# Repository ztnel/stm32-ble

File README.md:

# stm32-ble
STM32 Bluetooth Hardware Design Files

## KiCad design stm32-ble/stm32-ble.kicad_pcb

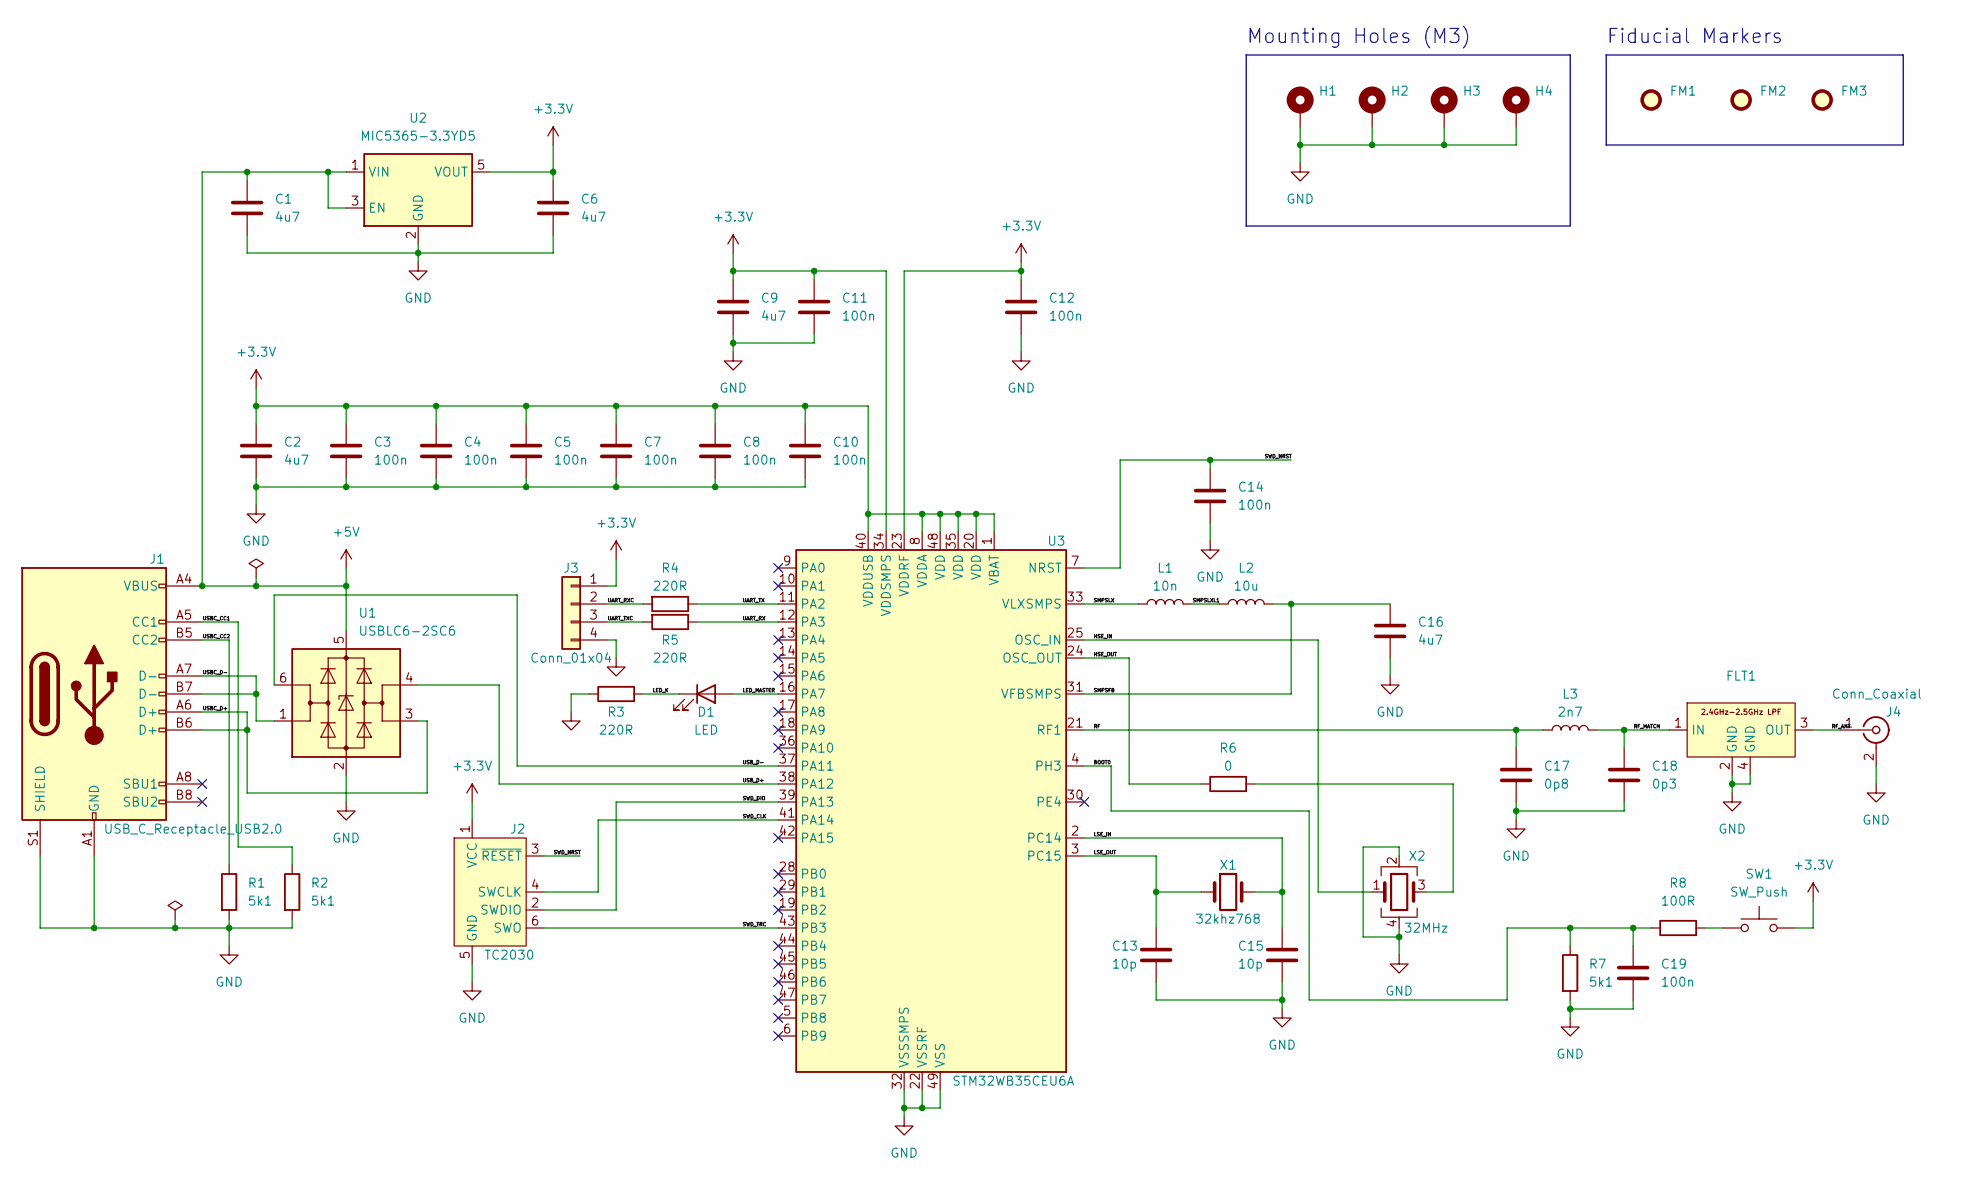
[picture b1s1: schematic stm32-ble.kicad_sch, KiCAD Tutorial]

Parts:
C1, C2, C6, C9, C16: 4u7; C_0603_1608Metric
C3, C4, C5, C7, C8, C10, C11, C12, C14, C19: 100n; C_0402_1005Metric
C13, C15: 10p; C_0402_1005Metric
C17: 0p8; C_0402_1005Metric
C18: 0p3; C_0402_1005Metric
D1: LED; LED_0402_1005Metric
FLT1: DLF162500LT-5028A1
FM1, FM2, FM3: Fiducial; Fiducial_1mm_Mask2mm
H1, H2, H3, H4: MountingHole_Pad; MountingHole_2.2mm_M2_Pad_Via
J1: USB_C_Receptacle_USB2.0; USB_C_Receptacle_GCT_USB4105-xx-A_16P_TopMnt_Horizontal
J2: TC2030; Tag-Connect_TC2030-IDC-FP_2x03_P1.27mm_Vertical
J3: Conn_01x04; Molex_PicoBlade_53048-0410_1x04_P1.25mm_Horizontal
J4: Conn_Coaxial; U.FL_Hirose_U.FL-R-SMT-1_Vertical
L1: 10n; L_0402_1005Metric
L2: 10u; L_0805_2012Metric
L3: 2n7; L_0402_1005Metric
R1, R2, R7: 5k1; R_0402_1005Metric
R3, R4, R5: 220R; R_0402_1005Metric
R6: 0; R_0402_1005Metric
R8: 100R; R_0402_1005Metric
SW1: SW_Push; SW_SPST_CK_RS282G05A3
U1: USBLC6-2SC6; SOT-23-6
U2: MIC5365-3.3YD5; SOT-23-5
U3: STM32WB35CEU6A; QFN-48-1EP_7x7mm_P0.5mm_EP5.6x5.6mm
X1: 32khz768; Crystal_SMD_2012-2Pin_2.0x1.2mm
X2: 32MHz; Crystal_SMD_2016-4Pin_2.0x1.6mm

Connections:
+3.3V: C2.1, C3.1, C4.1, C5.1, C6.1, C7.1, C8.1, C9.1, C10.1, C11.1, C12.1, J2.1 (VCC), J3.1, SW1.2, U2.5 (VOUT), U3.1 (VBAT), U3.8 (VDDA), U3.20 (VDD), U3.23 (VDDRF), U3.34 (VDDSMPS), U3.35 (VDD), U3.40 (VDDUSB), U3.48 (VDD)
+5V: C1.1, J1.A4 (VBUS), J1.A9 (VBUS), J1.B4 (VBUS), J1.B9 (VBUS), U1.5 (VBUS), U2.1 (VIN), U2.3 (EN)
/BOOT0: C19.1, R7.1, R8.1, U3.4 (PH3)
/HSE_IN: U3.25 (OSC_IN), X2.1
/HSE_OUT: R6.1, U3.24 (OSC_OUT)
/LED_K: D1.1 (K), R3.2
/LED_MASTER: D1.2 (A), U3.16 (PA7)
/LSE_IN: C15.1, U3.2 (PC14), X1.2
/LSE_OUT: C13.1, U3.3 (PC15), X1.1
/RF: C17.1, L3.1, U3.21 (RF1)
/RF_ANT: FLT1.3 (OUT), J4.1 (In)
/RF_MATCH: C18.1, FLT1.1 (IN), L3.2
/SMPSFB: C16.1, L2.2, U3.31 (VFBSMPS)
/SMPSLX: L1.1, U3.33 (VLXSMPS)
/SMPSLXL1: L1.2, L2.1
/SWD_CLK: J2.4 (SWCLK), U3.41 (PA14)
/SWD_DIO: J2.2 (SWDIO), U3.39 (PA13)
/SWD_NRST: C14.1, J2.3 (~RESET), U3.7 (NRST)
/SWD_TRC: J2.6 (SWO), U3.43 (PB3)
/UART_RX: R5.1, U3.12 (PA3)
/UART_RXC: J3.2, R4.2
/UART_TX: R4.1, U3.11 (PA2)
/UART_TXC: J3.3, R5.2
/USBC_CC1: J1.A5 (CC1), R2.1
/USBC_CC2: J1.B5 (CC2), R1.1
/USBC_D+: J1.A6 (D+), J1.B6 (D+), U1.3 (I/O2)
/USBC_D-: J1.A7 (D-), J1.B7 (D-), U1.1 (I/O1)
/USB_D+: U1.4 (I/O2), U3.38 (PA12)
/USB_D-: U1.6 (I/O1), U3.37 (PA11)
GND: C1.2, C2.2, C3.2, C4.2, C5.2, C6.2, C7.2, C8.2, C9.2, C10.2, C11.2, C12.2, C13.2, C14.2, C15.2, C16.2, C17.2, C18.2, C19.2, FLT1.2 (GND), FLT1.4 (GND), H1.1, H2.1, H3.1, H4.1, J1.A1 (GND), J1.A12 (GND), J1.B1 (GND), J1.B12 (GND), J1.S1 (SHIELD), J2.5 (GND), J3.4, J4.2 (Ext), R1.2, R2.2, R3.1, R7.2, U1.2 (GND), U2.2 (GND), U3.22 (VSSRF), U3.32 (VSSSMPS), U3.49 (VSS), X2.2, X2.4
unnamed: R6.2, X2.3
unnamed: R8.2, SW1.1

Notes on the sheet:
Fiducial Markers
Mounting Holes (M3)

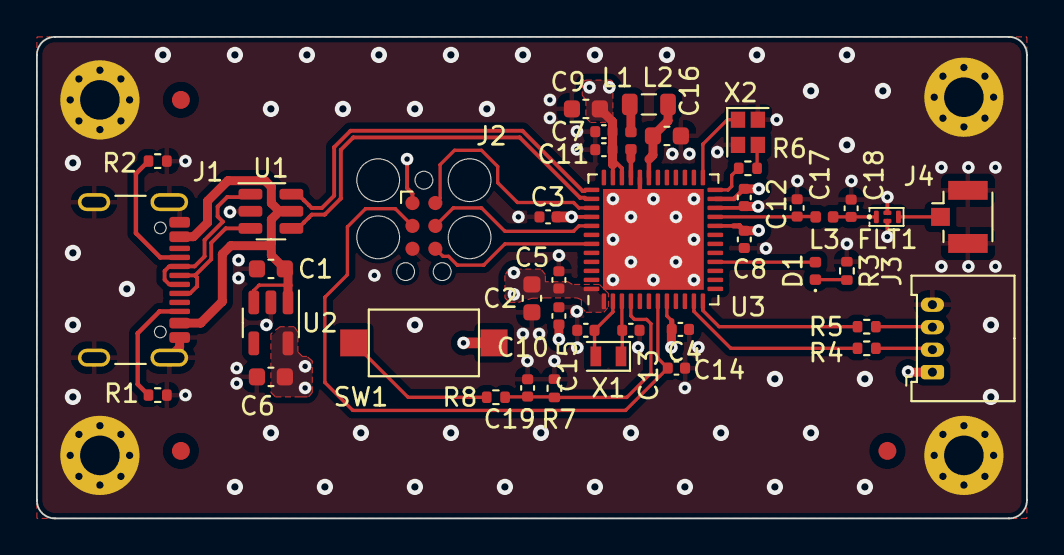
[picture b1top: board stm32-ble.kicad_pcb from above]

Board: 4 copper layers, 55.0 x 26.8 mm, 49 parts (0 on the bottom side), 32 nets.

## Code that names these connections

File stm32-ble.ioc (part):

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Mcu.Name=STM32WB35C(C-E)UxA
Mcu.Package=UFQFPN48
Mcu.UserName=STM32WB35CEUxA
PA11.Mode=Device
PA11.Signal=USB_DM
PA12.Mode=Device
PA12.Signal=USB_DP
PA13.Mode=Trace_Asynchronous_SW
PA13.Signal=SYS_JTMS-SWDIO
PA14.Mode=Trace_Asynchronous_SW
PA14.Signal=SYS_JTCK-SWCLK
PA2.Mode=Asynchronous
PA2.Signal=LPUART1_TX
PA3.Mode=Asynchronous
PA3.Signal=LPUART1_RX
PA7.Signal=S_TIM17_CH1
PB3.Mode=Trace_Asynchronous_SW
PB3.Signal=SYS_JTDO-SWO
PB6.Mode=I2C
PB6.Signal=I2C1_SCL
PB7.Mode=I2C
PB7.Signal=I2C1_SDA
PC14-OSC32_IN.Mode=LSE-External-Oscillator
PC14-OSC32_IN.Signal=RCC_OSC32_IN
PC15-OSC32_OUT.Mode=LSE-External-Oscillator
PC15-OSC32_OUT.Signal=RCC_OSC32_OUT
RCC.HSE_VALUE=8000000
board=custom

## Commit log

2023-12-27 schematic capture
2023-12-27 pinmux
2023-12-30 pcb layout
2023-12-30 ignore backups
2024-01-02 fiducials, mounting holes and preliminary via placement
